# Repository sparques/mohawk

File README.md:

# Mohawk

Mohawk is a Raspberry Pi Zero µHAT-sized UHF/VHF radio interface built around a DRA818 radio module which comes in a UHF and a VHF variant (DRA818U / DRA818V). It brings the radio's audio, configuration UART, and push-to-talk control to a Raspberry Pi, and provides an RS-232 port for an external device. The current design is a KiCad 10 schematic and two-layer PCB. Hardware validation has not been recorded in this repository.

Linux has drivers for both the SPI UART interface and the codec, so two hardware TTYs show up and the codec shows up as a regular alsa soundcard. 

## Project files

| Path | Contents |
| --- | --- |
| [`mohawk/mohawk.kicad_pro`](mohawk/mohawk.kicad_pro) | KiCad project; open this file to work on the design. |
| [`mohawk/mohawk.kicad_sch`](mohawk/mohawk.kicad_sch) | Main schematic: Pi header, radio, UART bridge, RS-232, and HAT ID EEPROM. |
| [`mohawk/soundChip.kicad_sch`](mohawk/soundChip.kicad_sch) | Hierarchical sheet for the audio codec and speaker output. |
| [`mohawk-overlay.dts`](mohawk-overlay.dts) | Raspberry Pi Zero Device Tree overlay for the SPI UART and codec sound card. |
| [`mohawk/mohawk.kicad_pcb`](mohawk/mohawk.kicad_pcb) | Routed, approximately 65 × 30 mm, two-layer PCB. |
| [`mohawk/lib/`](mohawk/lib/) | Project-specific symbols, footprints, and 3D models. |
| [`datasheets/`](datasheets/) | Local copies of component datasheets. |

The schematic and board were saved with KiCad 10. Custom footprints use `${KIPRJMOD}/lib/KiCADv6/footprints.pretty`.

## Hardware overview

| Reference | Part | Role | Datasheet |
| --- | --- | --- | --- |
| U3 | DRA818 radio module (VHF variant intended) | RF transceiver; UART configuration, analog audio, PTT, squelch, and power-down signals | [DRA818V](datasheets/DRA818V.pdf) |
| U5 | TLV320AIC3204 | SPI-controlled audio codec with I²S/PCM audio to the Pi | [TLV320AIC3204](datasheets/tlv320aic3204.pdf) |
| U2 | SC16IS752 | SPI-to-dual-UART bridge: one channel for the radio, one for external serial | [SC16IS752](datasheets/SC16IS752_SC16IS762.pdf) |
| U4 | ‎MAX3232 | Converts the external UART channel to RS-232 levels | [‎MAX3232E](datasheets/max3232e.pdf) |
| U1 | CAT24C256 | Raspberry Pi HAT identification EEPROM on the dedicated ID I²C pins | — |
| Y1 | 1.8432 MHz oscillator | Clock for the SC16IS752 | [Abracon ASE series](datasheets/ASEseries.pdf) |

The BoM will be finalized once a verified working prototype has been assembled and specific part variants have been nailed down and confirmed good.

The Pi's SPI0 bus is shared by the UART bridge (CE1) and codec (CE0). The codec's digital audio uses the Pi's PCM/I²S pins. The bridge's two UART channels connect separately to the DRA818 and ‎MAX3232, leaving the Pi's built-in UART pins available on the 40-pin header. The codec connects to the radio's analog input and output; its `GPIO_MFP5` pin drives the radio's PTT net. The codec's right headphone output feeds the two-pin speaker connection through a coupling capacitor.

## Functional Diagram

## External connections

Pin numbers below come from the current schematic/netlist. Check the PCB pad numbering and your cable orientation before attaching hardware.

| Connector | Connection |
| --- | --- |
| J1 | 2 × 20 Raspberry Pi GPIO socket; supplies 5 V and 3.3 V and carries SPI0, PCM/I²S, I²C, and control GPIOs. |
| J2 | SMA antenna connector wired to the DRA818 `ANT` pin. |
| J3 | Five SMD pads for a UI board: 1 `GPIO17`, 2 GND, 3 `GPIO3/SCL1`, 4 `GPIO2/SDA1`, 5 +5 V. |
| J4 | Five SMD pads labeled “DB9 Header”: 1 `RS232_RX`, 2 `RS232_TX`, 3 `RS232_CTS`, 4 `RS232_RTS`, 5 GND. An external cable/connector is needed for a DB9 interface. |
| LS1 | Two-pin speaker header: codec headphone output via C18 and GND. |
| WP1 | Open solder jumper for EEPROM write protection; closing it connects the EEPROM's `WP` pin to 3.3 V. |

J3 carries **5 V power** but uses the Pi's **3.3 V GPIO/I²C signals**. `GPIO17` Is brought out for use as an interrupt, but is just a GPIO pin, so it could be used for an idicator LED or a button, etc. Use the netlist/pin table above when wiring a UI board.

There is no USB UART or 2 × 5 IDC RS-232 connector in the current schematic. The external serial connection is the ‎MAX3232 and J4's five SMD pads.

The HAT ID EEPROM uses `ID_SDA`/`ID_SCL` on J1 pins 27/28. Those are separate from the ordinary I²C1 pins used at J3. The Device Tree overlay is present but has not been tested on hardware.

## Control signals on the Pi header

| Pi GPIO (physical pin) | Connected function |
| --- | --- |
| GPIO5 (29) | SC16IS752 reset |
| GPIO7 / SPI0 CE1 (26) | SC16IS752 chip select |
| GPIO8 / SPI0 CE0 (24) | TLV320AIC3204 chip select |
| GPIO18–21 (12, 35, 38, 40) | Codec bit clock, word clock, data to Pi, and data from Pi |
| GPIO22 (15) | DRA818 power-down (`PD`) |
| GPIO23 (16) | DRA818 squelch (`SQ`) |
| GPIO25 (22) | SC16IS752 interrupt |
| GPIO27 (13) | Codec reset |

The radio's `PTT` is connected to the codec's multifunction GPIO rather than directly to a Pi GPIO. Software must configure that codec pin before attempting to transmit. These are schematic connections, not a tested Linux setup or a promise of a particular `/dev/tty*` assignment.

## Device Tree overlay

The overlay targets the Raspberry Pi Zero family. It enables SPI0 with the codec on CE0 and the SC16IS752 on CE1, enables I²S, and creates a simple ALSA sound card. UART channel A connects to the DRA818; channel B connects to the MAX3232. The bridge's interrupt and reset use GPIO25 and GPIO5. The codec reset uses GPIO27.

**Fit R15 (10 Ω) before using the codec.** The schematic marks it do-not-populate, but it is the only connection from GPIO4/GPCLK0 to the codec MCLK pin. The overlay supplies a 12.288 MHz master clock on that pin. With R15 absent, the audio clock is disconnected regardless of Device Tree configuration.

On a Raspberry Pi with the kernel Device Tree headers installed, compile and install the overlay:

```sh
cpp -nostdinc -undef -D__DTS__ -I /lib/modules/$(uname -r)/build/include -x assembler-with-cpp mohawk-overlay.dts /tmp/mohawk-overlay.dts
dtc -@ -I dts -O dtb -o mohawk.dtbo /tmp/mohawk-overlay.dts
sudo cp mohawk.dtbo /boot/firmware/overlays/
```

Add `dtoverlay=mohawk` to `/boot/firmware/config.txt` and reboot. On systems using `/boot/overlays` and `/boot/config.txt`, use those paths instead. The HAT ID EEPROM is not programmed by this overlay; add the `dtoverlay` line explicitly until it is.

The codec's MFP5 pin is initialized high so the radio's active-low PTT stays released. Its ALSA `MFP5 GPIO` control can later drive it low to transmit; ensure the control is set high again when transmission ends. The overlay also describes the radio receive audio on `IN1_L`, transmit audio on `LOL`, and the monitor headphone output on `HPR`. Audio mixer routing and levels still need to be set in ALSA and verified on a prototype.

## Design and build status

The PCB is routed in the saved design, and KiCad reports no unconnected items. A KiCad 10 check of this checkout found **26 ERC violations, 59 PCB DRC violations, and two schematic/PCB footprint-name parity warnings**. The DRC findings include silk overlap, copper-to-edge and hole-clearance errors, alongside warnings about copper islands, dangling copper, footprint library matches, and text thickness. Review and resolve the reports in KiCad before ordering boards. The schematic also marks R5, R10, R14, and R15 as do-not-populate.

To rerun the checks and export a BOM from the project root:

```sh
kicad-cli sch erc -o /tmp/mohawk-erc.rpt mohawk/mohawk.kicad_sch
kicad-cli pcb drc --schematic-parity -o /tmp/mohawk-drc.rpt mohawk/mohawk.kicad_pcb
kicad-cli sch export bom -o /tmp/mohawk-bom.csv mohawk/mohawk.kicad_sch
```

## Build Notes

U1 (the I²C EEPROM) and U4 (MAX3232) are technically optional. You do not need the MAX32322 or its supporting passives if you do not need RS-232 support. The I2C EEPROM lets a DeviceTree overlay be automatically loaded at boot so linux kernel modules know what the pin assignments are, but this is just a convenience and also not strictly required.

## Legal Notice

Neither this device nor the DRA818 module is, obviously, certified by the FCC. Only a suitably licensed individual may transmit using this device: you must have an amateur radio license. It is up to the operator to ensure they are following FCC requirements.

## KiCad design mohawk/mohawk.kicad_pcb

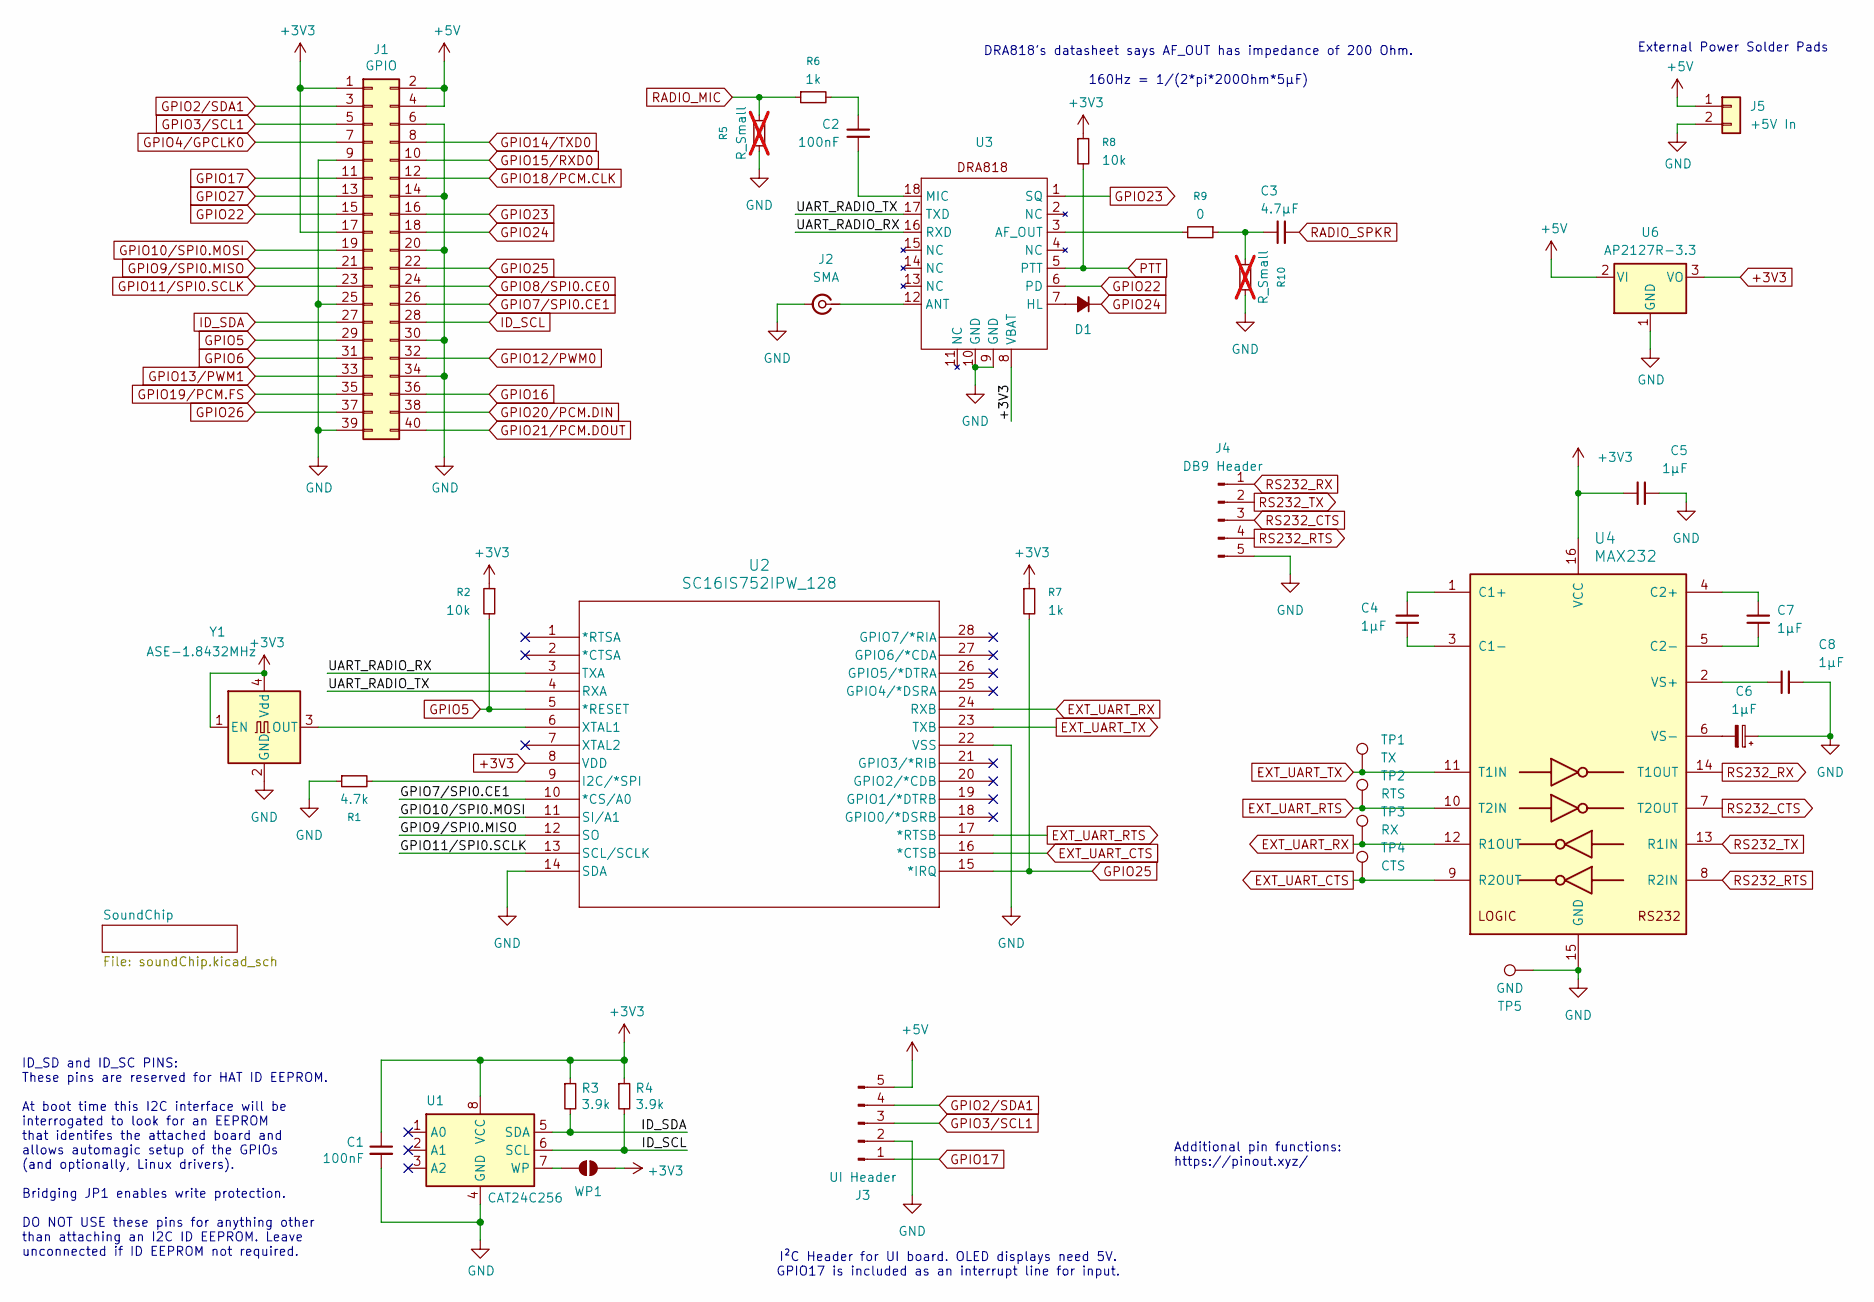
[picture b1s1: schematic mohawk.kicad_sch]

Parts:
C1, C2: 100nF; C_0805_2012Metric
C3: 4.7µF; C_0805_2012Metric
C4, C5, C6, C7, C8: 1µF; C_0805_2012Metric
D1: D_0805_2012Metric
J1: GPIO; PinSocket_2x20_P2.54mm_Vertical
J2: SMA; SMA_BAT_Wireless_BWSMA-KWE-Z001
J3: UI Header; 1x05 SMD pads
J4: DB9 Header; 1x05 SMD pads
J5: +5V In; SolderWirePad 1x02
R1: 4.7k; R_0805_2012Metric
R2, R8: 10k; R_0805_2012Metric
R3, R4: 3.9k; R_0805_2012Metric
R5, R10: R_Small; R_0805_2012Metric; not fitted
R6, R7: 1k; R_0805_2012Metric
R9: 0; R_0805_2012Metric
TP1: TX; TestPoint_Pad_D1.0mm
TP2: RTS; TestPoint_Pad_D1.0mm
TP3: RX; TestPoint_Pad_D1.0mm
TP4: CTS; TestPoint_Pad_D1.0mm
TP5: GND; TestPoint_Pad_D1.0mm
U1: CAT24C256; SOIC8_ONS
U2: SC16IS752IPW_128; TSSOP28_SOT361-1_NXP
U3: DRA818
U4: MAX232; PW16
U6: AP2127R-3.3; SOT-89-3
WP1: ID_WP; SolderJumper-2_P1.3mm_Open_Pad1.0x1.5mm
Y1: ASE-1.8432MHz; Oscillator_SMD_Abracon_ASE-4Pin_3.2x2.5mm

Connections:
+3V3: C1.1, C5.2, J1.1, J1.17, R2.1, R3.1, R4.1, R7.1, R8.1, U1.8 (VCC), U2.8 (VDD), U3.8 (VBAT), U4.16 (VCC), U6.3 (VO), WP1.2 (B), Y1.1 (EN), Y1.4 (Vdd); also elsewhere on the board
+5V: J1.2, J1.4, J3.5, J5.1, U6.2 (VI)
/UART_RADIO_RX: U2.3 (TXA), U3.16 (RXD)
/UART_RADIO_TX: U2.4 (RXA), U3.17 (TXD)
EXT_UART_CTS: TP4.1 (1_1), U2.16 (*CTSB), U4.9 (R2OUT)
EXT_UART_RTS: TP2.1 (1_1), U2.17 (*RTSB), U4.10 (T2IN)
EXT_UART_RX: TP3.1 (1_1), U2.24 (RXB), U4.12 (R1OUT)
EXT_UART_TX: TP1.1 (1_1), U2.23 (TXB), U4.11 (T1IN)
GND: C1.2, C5.1, C6.1, C8.2, J1.6, J1.9, J1.14, J1.20, J1.25, J1.30, J1.34, J1.39, J2.2 (Ext), J3.2, J4.5, J5.2, R1.1, R5.1, R10.1, TP5.1 (1_1), U1.4 (GND), U2.14 (SDA), U2.22 (VSS), U3.9 (GND), U3.10 (GND), U4.15 (GND), U6.1 (GND), Y1.2 (GND); also elsewhere on the board
GPIO2/SDA1: J1.3, J3.4
GPIO3/SCL1: J1.5, J3.3
GPIO4/GPCLK0: J1.7; also elsewhere on the board
GPIO5: J1.29, R2.2, U2.5 (*RESET)
GPIO6: J1.31
GPIO7/SPI0.CE1: J1.26, U2.10 (*CS/A0)
GPIO8/SPI0.CE0: J1.24; also elsewhere on the board
GPIO9/SPI0.MISO: J1.21, U2.12 (SO); also elsewhere on the board
GPIO10/SPI0.MOSI: J1.19, U2.11 (SI/A1); also elsewhere on the board
GPIO11/SPI0.SCLK: J1.23, U2.13 (SCL/SCLK); also elsewhere on the board
GPIO12/PWM0: J1.32
GPIO13/PWM1: J1.33
GPIO14/TXD0: J1.8
GPIO15/RXD0: J1.10
GPIO16: J1.36
GPIO17: J1.11, J3.1
GPIO18/PCM.CLK: J1.12; also elsewhere on the board
GPIO19/PCM.FS: J1.35; also elsewhere on the board
GPIO20/PCM.DIN: J1.38; also elsewhere on the board
GPIO21/PCM.DOUT: J1.40; also elsewhere on the board
GPIO22: J1.15, U3.6 (PD)
GPIO23: J1.16, U3.1 (SQ)
GPIO24: D1.1 (K), J1.18
GPIO25: J1.22, R7.2, U2.15 (*IRQ)
GPIO26: J1.37
GPIO27: J1.13; also elsewhere on the board
ID_SCL: J1.28, R4.2, U1.6 (SCL)
ID_SDA: J1.27, R3.2, U1.5 (SDA)
unnamed: C2.1, R6.2
unnamed: C3.1, R9.1, R10.2
unnamed: D1.2 (A), U3.7 (HL)
unnamed: J2.1 (In), U3.12 (ANT)
unnamed: U1.7 (WP), WP1.1 (A)
unnamed: R1.2, U2.9 (I2C/*SPI)
unnamed: U2.6 (XTAL1), Y1.3 (OUT)
unnamed: R9.2, U3.3 (AF_OUT)
unnamed: C2.2, U3.18 (MIC)
unnamed: C4.1, U4.1 (C1+)
unnamed: C4.2, U4.3 (C1-)
unnamed: C7.2, U4.4 (C2+)
unnamed: C7.1, U4.5 (C2-)
unnamed: C8.1, U4.2 (VS+)
unnamed: C6.2, U4.6 (VS-)
PTT: R8.2, U3.5 (PTT); also elsewhere on the board
RADIO_MIC: R5.2, R6.1; also elsewhere on the board
RADIO_SPKR: C3.2; also elsewhere on the board
RS232_CTS: J4.3, U4.7 (T2OUT)
RS232_RTS: J4.4, U4.8 (R2IN)
RS232_RX: J4.1, U4.14 (T1OUT)
RS232_TX: J4.2, U4.13 (R1IN)

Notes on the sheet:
I²C Header for UI board. OLED displays need 5V. GPIO17 is included as an interrupt line for input.
ID_SD and ID_SC PINS: These pins are reserved for HAT ID EEPROM. At boot time this I2C interface will be interrogated to look for an EEPROM that identifes the attached board and allows automagic setup of the GPIOs (and optionally, Linux drivers). Bridging JP1 enables write protection. DO NOT USE th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
DRA818's datasheet says AF_OUT has impedance of 200 Ohm. 160Hz = 1/(2*pi*200Ohm*5µF)
External Power Solder Pads
Additional pin functions: https://pinout.xyz/

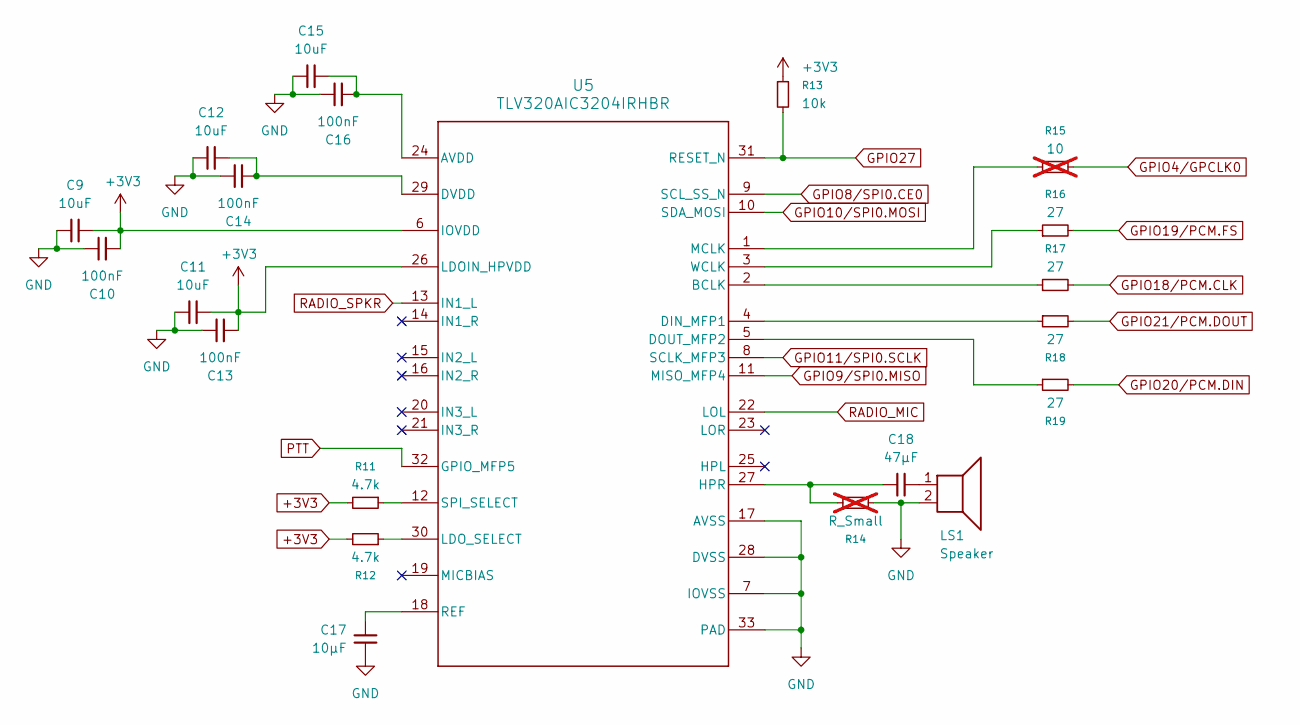
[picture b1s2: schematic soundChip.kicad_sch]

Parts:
C9, C11, C12, C15: 10uF; C_0805_2012Metric
C10, C13, C14, C16: 100nF; C_0805_2012Metric
C17: 10µF; C_0805_2012Metric
C18: 47µF; C_0805_2012Metric
LS1: Speaker; PinHeader_1x02_P2.54mm_Vertical
R11, R12: 4.7k; R_0805_2012Metric
R13: 10k; R_0805_2012Metric
R14: R_Small; R_0805_2012Metric; not fitted
R15: 10; R_0805_2012Metric; not fitted
R16, R17, R18, R19: 27; R_0805_2012Metric
U5: TLV320AIC3204IRHBR; RHB0032E_NV

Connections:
+3V3: C9.2, C10.2, C11.2, C13.2, R11.2, R12.2, R13.1, U5.6 (IOVDD), U5.26 (LDOIN_HPVDD); also elsewhere on the board
GND: C9.1, C10.1, C11.1, C12.1, C13.1, C14.1, C15.1, C16.1, C17.2, LS1.2, R14.2, U5.7 (IOVSS), U5.17 (AVSS), U5.28 (DVSS), U5.33 (PAD); also elsewhere on the board
GPIO4/GPCLK0: R15.2; also elsewhere on the board
GPIO8/SPI0.CE0: U5.9 (SCL_SS_N); also elsewhere on the board
GPIO9/SPI0.MISO: U5.11 (MISO_MFP4); also elsewhere on the board
GPIO10/SPI0.MOSI: U5.10 (SDA_MOSI); also elsewhere on the board
GPIO11/SPI0.SCLK: U5.8 (SCLK_MFP3); also elsewhere on the board
GPIO18/PCM.CLK: R17.2; also elsewhere on the board
GPIO19/PCM.FS: R16.2; also elsewhere on the board
GPIO20/PCM.DIN: R19.2; also elsewhere on the board
GPIO21/PCM.DOUT: R18.2; also elsewhere on the board
GPIO27: R13.2, U5.31 (RESET_N); also elsewhere on the board
unnamed: C18.2, LS1.1
unnamed: C15.2, C16.2, U5.24 (AVDD)
unnamed: R17.1, U5.2 (BCLK)
unnamed: R18.1, U5.4 (DIN_MFP1)
unnamed: R19.1, U5.5 (DOUT_MFP2)
unnamed: C12.2, C14.2, U5.29 (DVDD)
unnamed: C18.1, R14.1, U5.27 (HPR)
unnamed: R12.1, U5.30 (LDO_SELECT)
unnamed: R15.1, U5.1 (MCLK)
unnamed: C17.1, U5.18 (REF)
unnamed: R11.1, U5.12 (SPI_SELECT)
unnamed: R16.1, U5.3 (WCLK)
PTT: U5.32 (GPIO_MFP5); also elsewhere on the board
RADIO_MIC: U5.22 (LOL); also elsewhere on the board
RADIO_SPKR: U5.13 (IN1_L); also elsewhere on the board

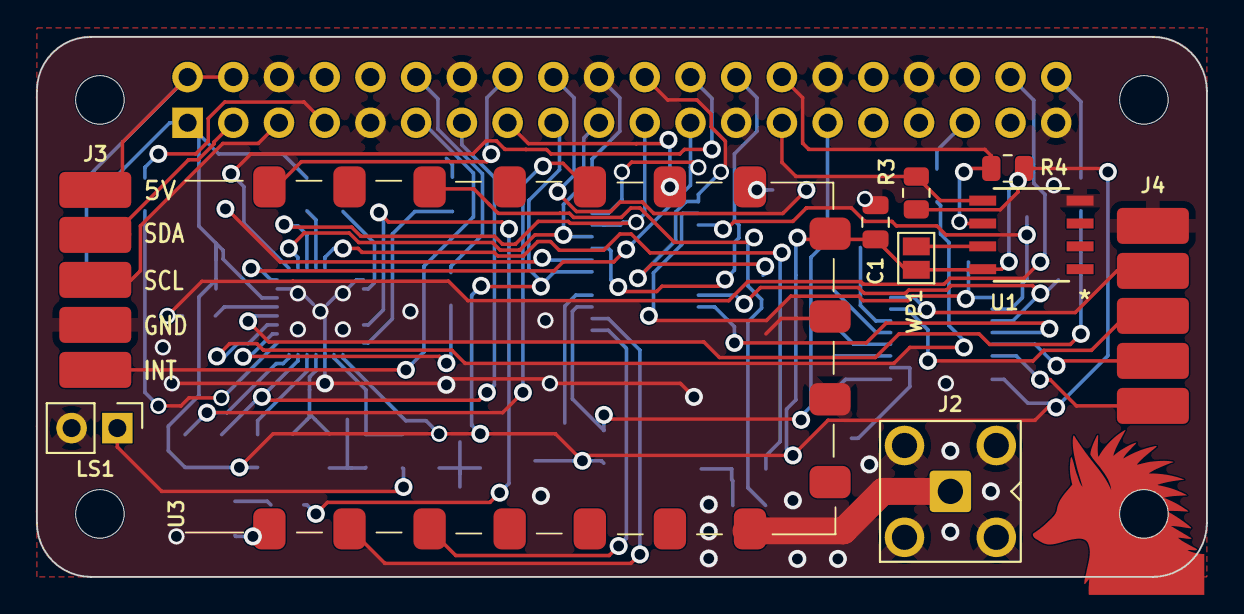
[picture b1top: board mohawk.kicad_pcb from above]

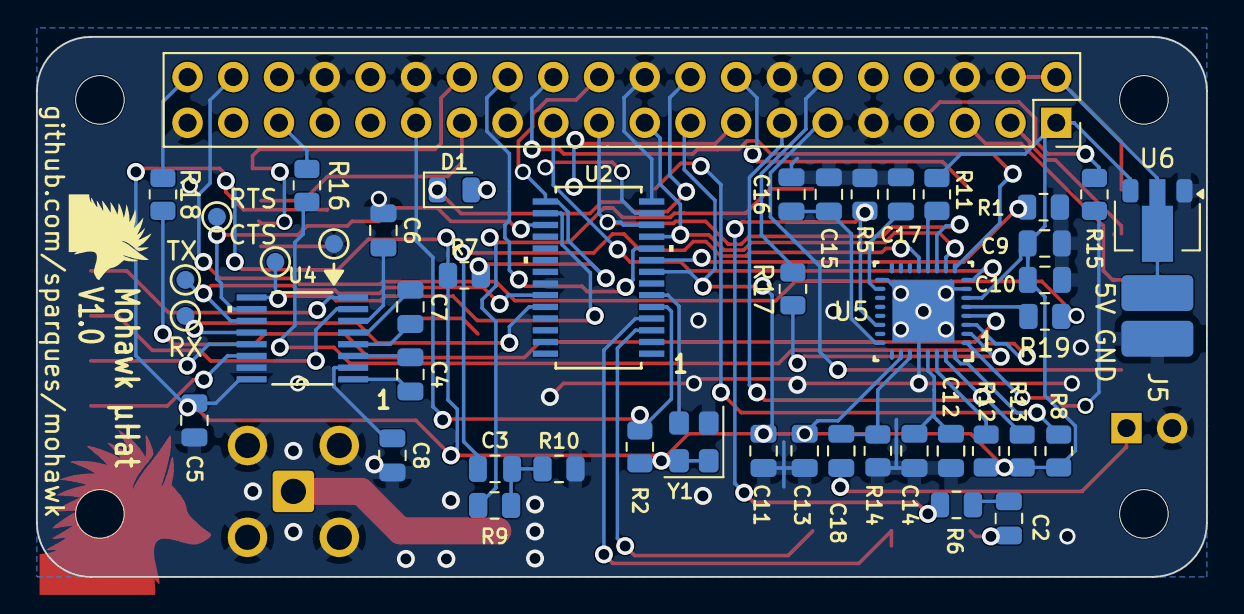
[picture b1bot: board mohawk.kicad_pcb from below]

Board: 2 copper layers, 65.0 x 30.0 mm, 61 parts (47 on the bottom side), 64 nets.

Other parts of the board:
MH1, MH2, MH3, MH4: MountingHole_2.7mm_M2.5
